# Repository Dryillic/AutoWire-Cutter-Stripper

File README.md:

# AutoWire-Cutter-Stripper

This repository is for documenting the process and project of creating our own automatic wire cutter.
The device will be able to take input from the user regarding wire length, options and number of wires.

The original inspiration for this project came from Reddit user "Maclsk" on the subreddit /r/specializedtools, link here: https://www.reddit.com/r/specializedtools/comments/78wd32/i_made_a_specialized_tool_for_cutting_wire/
Our goal is to create a similar device with autostripping for our workplace.

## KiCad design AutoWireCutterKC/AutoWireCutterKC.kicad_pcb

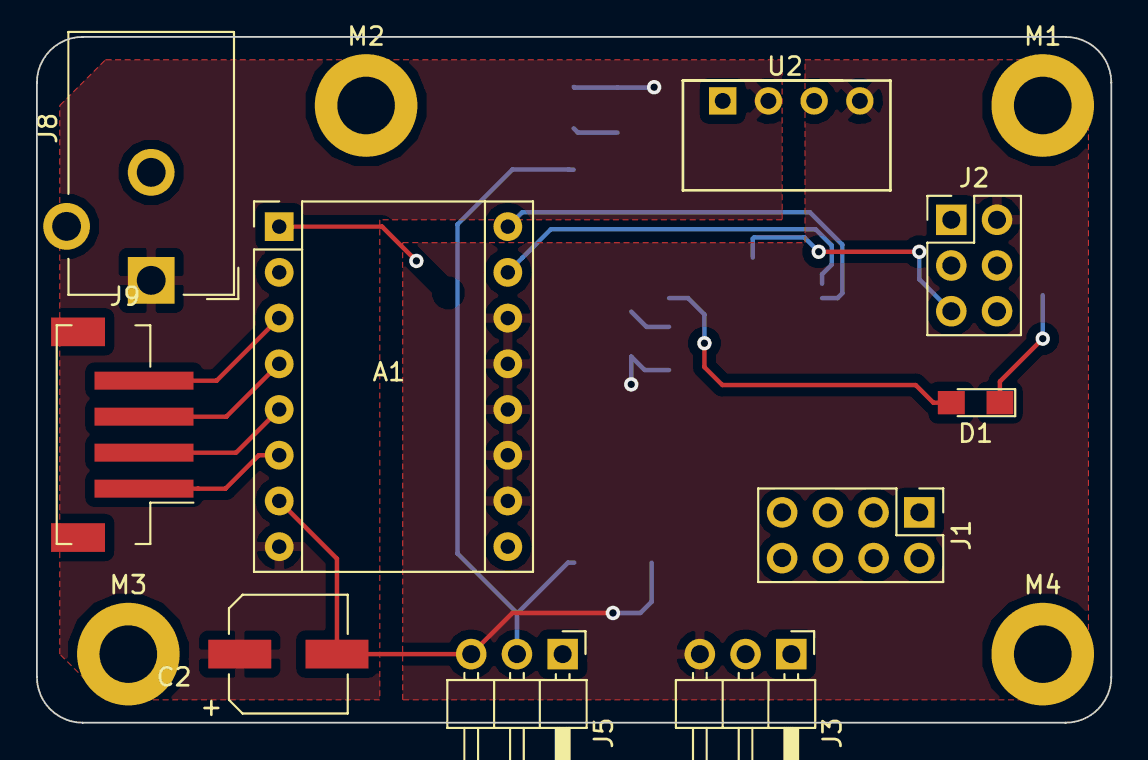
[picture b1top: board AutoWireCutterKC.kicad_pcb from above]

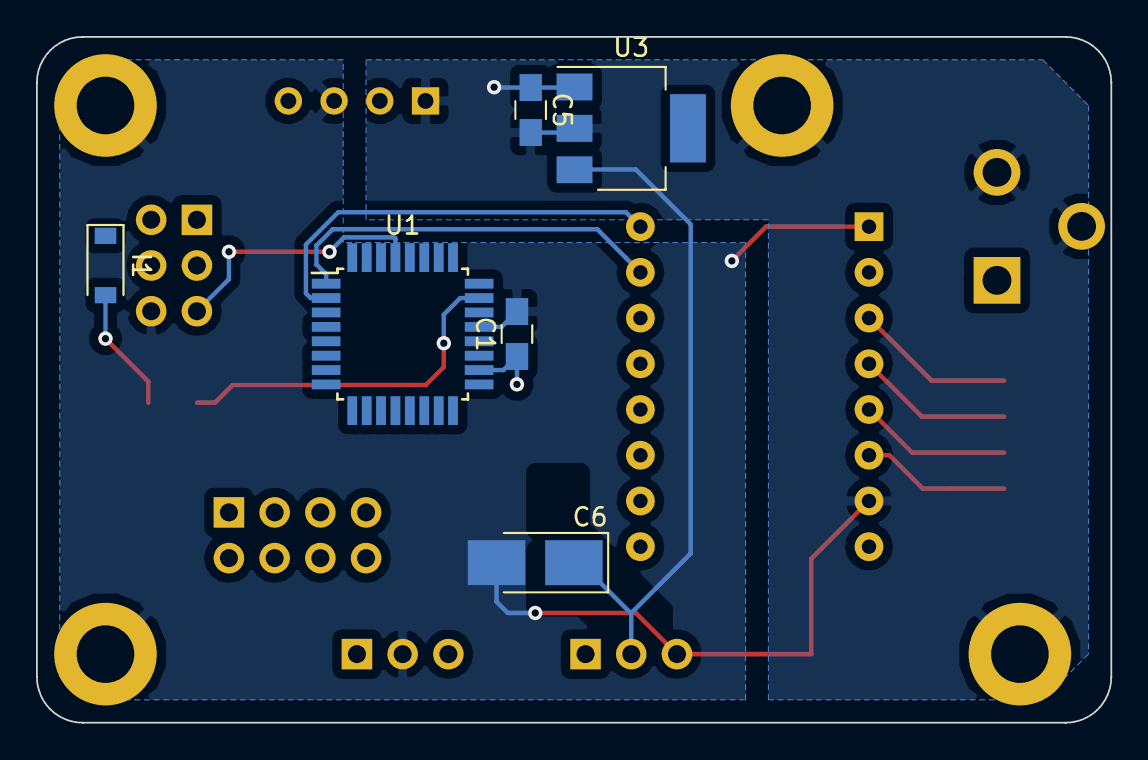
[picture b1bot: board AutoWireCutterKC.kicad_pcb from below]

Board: 2 copper layers, 59.7 x 38.1 mm, 20 parts (6 on the bottom side), 25 nets.

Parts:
A1: Pololu_Breakout_DRV8825; Pololu_Breakout-16_15.2x20.3mm
C1: 100n; C_0805_HandSoldering
C2: 100u; CP_Elec_6.3x7.7
C5: 1u; C_0805_HandSoldering
C6: 3.3u; CP_Tantalum_Case-B_EIA-3528-21_Hand
D1: LED; LED_0805_HandSoldering
I1: NSI50010YT1G; D_SOD-123
J1: LCD I/O; Pin_Header_Straight_2x04_Pitch2.54mm
J2: ISP; Pin_Header_Straight_2x03_Pitch2.54mm
J3: LCD; Pin_Header_Angled_1x03_Pitch2.54mm
J5: Servo; Pin_Header_Angled_1x03_Pitch2.54mm
J8: Barrel_Jack; Barrel_Jack_CUI_PJ-102AH
J9: Stepper; JST_PH_B4B_StressReliefCorrect
M1, M2, M3, M4: Conn_01x01_Male; MountingHole_3.2mm_M3_ISO7380_Pad
U1: ATMEGA328P-AU; TQFP-32_7x7mm_Pitch0.8mm
U2: CRE1S1205SC; CRE1S1205SC_DC_to_DC
U3: LT1129-5.0_SOT223; SOT-223

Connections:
+5V: C6.1, J5.2, U3.3
+5VL: A1.10, A1.11, A1.12, A1.13, A1.14, C1.1, J2.2, J3.3, U1.4, U1.6, U1.18, U2.4
+12V: A1.8, C2.1, C5.1, J8.1, U2.2, U3.1
GND: A1.7, C2.2, C5.2, C6.2, I1.1, J5.3, J8.2, J8.3, M2.1, M3.1, U2.1, U3.2
GNDREF: A1.1, C1.2, J2.6, J3.2, M1.1, M4.1, U1.3, U1.5, U1.21, U2.3
unnamed: A1.3, J9.4
unnamed: A1.4, J9.3
unnamed: A1.5, J9.2
unnamed: A1.6, J9.1
unnamed: A1.9, U1.32
unnamed: A1.15, U1.1
unnamed: A1.16, U1.2
unnamed: D1.1, I1.2
unnamed: D1.2, U1.23
unnamed: J1.1, U1.12
unnamed: J1.2, U1.13
unnamed: J1.3, U1.14
unnamed: J1.4, J2.4, U1.15
unnamed: J1.5, J2.1, U1.16
unnamed: J1.6, J2.3, U1.17
unnamed: J1.7, U1.7
unnamed: J1.8, U1.8
unnamed: J2.5, U1.29
unnamed: J3.1, U1.31
unnamed: J5.1, U1.10

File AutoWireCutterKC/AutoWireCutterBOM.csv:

Source:,C:/Users/dnatov/Documents/GitHub/AutoWire-Cutter-Stripper/AutoWireCutterKC/AutoWireCutterKC.sch,,,,,
Date:,6/14/2018 12:04,,,,,
Tool:,Eeschema 4.0.7,,,,,
Generator:,C:/Program Files (x86)/KiCad/bin/scripting/plugins/bom_csv_grouped_by_value.py,,,,,
Component Count:,20,,,,,
,,,,,,
Individual Components:,,,,,,
,,,,,,
Item,Qty,Reference(s),Value,LibPart,Footprint,Datasheet
,,A1,Pololu_Breakout_DRV8825,Driver_Motor:Pololu_Breakout_DRV8825,Module:Pololu_Breakout-16_15.2x20.3mm,
,,C1,100n,device:C,Capacitors_SMD:C_0805_HandSoldering,
,,C2,100u,device:CP,Capacitors_SMD:CP_Elec_6.3x7.7,
,,C3,1u,device:C,Capacitors_SMD:C_0805_HandSoldering,
,,C4,1u,device:C,Capacitors_SMD:C_0805_HandSoldering,
,,C5,1u,device:C,Capacitors_SMD:C_0805_HandSoldering,
,,C6,3.3u,device:CP1,Capacitors_Tantalum_SMD:CP_Tantalum_Case-B_EIA-3528-21_Hand,
,,J1,LCD I/O,conn:Conn_01x08,Pin_Headers:Pin_Header_Straight_2x04_Pitch2.54mm,
,,J2,ISP,conn:Conn_02x03_Odd_Even,Pin_Headers:Pin_Header_Straight_2x03_Pitch2.54mm,
,,J3,LCD Serial,conn:Conn_01x02,Pin_Headers:Pin_Header_Angled_1x02_Pitch2.54mm,
,,J5,LCD Power,conn:Conn_01x02,Pin_Headers:Pin_Header_Angled_1x02_Pitch2.54mm,
,,J6,Servo,conn:Conn_01x03,Pin_Headers:Pin_Header_Angled_1x03_Pitch2.54mm,
,,J8,Barrel_Jack,conn:Barrel_Jack,Connectors:Barrel_Jack_CUI_PJ-102AH,
,,J9,Stepper,conn:Conn_01x04,S4B-PH-SM4-TB,
,,M1,Conn_01x01_Male,conn:Conn_01x01_Male,,
,,M2,Conn_01x01_Male,conn:Conn_01x01_Male,,
,,M3,Conn_01x01_Male,conn:Conn_01x01_Male,,
,,U1,ATMEGA328P-AU,atmel:ATMEGA328P-AU,Housings_QFP:TQFP-32_7x7mm_Pitch0.8mm,
,,U2,MCP1700_SOT23,regul:MCP1700-5002E_SOT23,TO_SOT_Packages_SMD:SOT-23,
,,U3,LT1129-5.0_SOT223,regul:LT1129-5.0_SOT223,TO_SOT_Packages_SMD:SOT-223,
,,,,,,
,,,,,,
,,,,,,
Collated Components:,,,,,,
,,,,,,
Item,Qty,Reference(s),Value,LibPart,Footprint,Datasheet
1,1,A1,Pololu_Breakout_DRV8825,Driver_Motor:Pololu_Breakout_DRV8825,Module:Pololu_Breakout-16_15.2x20.3mm,
2,1,C1,100n,device:C,Capacitors_SMD:C_0805_HandSoldering,
3,1,C2,100u,device:CP,Capacitors_SMD:CP_Elec_6.3x7.7,
4,3,"C3, C4, C5",1u,device:C,Capacitors_SMD:C_0805_HandSoldering,
5,1,C6,3.3u,device:CP1,Capacitors_Tantalum_SMD:CP_Tantalum_Case-B_EIA-3528-21_Hand,
6,1,J1,LCD I/O,conn:Conn_01x08,Pin_Headers:Pin_Header_Straight_2x04_Pitch2.54mm,
7,1,J2,ISP,conn:Conn_02x03_Odd_Even,Pin_Headers:Pin_Header_Straight_2x03_Pitch2.54mm,
8,1,J3,LCD Serial,conn:Conn_01x02,Pin_Headers:Pin_Header_Angled_1x02_Pitch2.54mm,
9,1,J5,LCD Power,conn:Conn_01x02,Pin_Headers:Pin_Header_Angled_1x02_Pitch2.54mm,
10,1,J6,Servo,conn:Conn_01x03,Pin_Headers:Pin_Header_Angled_1x03_Pitch2.54mm,
11,1,J8,Barrel_Jack,conn:Barrel_Jack,Connectors:Barrel_Jack_CUI_PJ-102AH,
12,1,J9,Stepper,conn:Conn_01x04,Pin_Headers:Pin_Header_Straight_1x04_Pitch2.54mm,
13,3,"M1, M2, M3",Conn_01x01_Male,conn:Conn_01x01_Male,,
14,1,U1,ATMEGA328P-AU,atmel:ATMEGA328P-AU,Housings_QFP:TQFP-32_7x7mm_Pitch0.8mm,
15,1,U2,MCP1700_SOT23,regul:MCP1700-5002E_SOT23,TO_SOT_Packages_SMD:SOT-23,
16,1,U3,LT1129-5.0_SOT223,regul:LT1129-5.0_SOT223,TO_SOT_Packages_SMD:SOT-223,

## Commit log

2018-01-05 Add files via upload
    Serial Tx/Rx enable for the 328P. Also sets up a stream to serial so "printf" can be used to send ascii to a serial target.
2018-01-15 Add files via upload
    4x4 Keypad and LCD to display it. Still needs refining. Keypad input not saved, just a general read of a 4x4 pad.
2018-05-20 Added Stepper Library and Test Code
2018-05-20 Added demo video of Stepper Driver
2018-05-20 Updated library with working Runtostep function
    Additionally added better explanation of Runtostep in example main
2018-05-26 Create Servo Library Folder
2018-05-26 Added Servo Library and Ex Code
2018-05-26 Move to Stepper Library Folder
2018-05-26 Move ex code to StepperLibrary Folder
2018-06-05 Adding KiCad Files
2018-06-06 Update uC Layout
    Power is next, runout sensor planned.
2018-06-11 Schematic Finished
    TODO: Double check connections
2018-06-12 Working on footprints
    in progress
2018-06-12 Finished Footprints
    Refer to sch for generating BOM
2018-06-12 PCB Populated
    Traces needed
2018-06-12 Moving around footprints
    Changing spacing and connectors
2018-06-13 PCB Redesign
    Started on traces
2018-06-13 Rewiring - Layout changed again...
2018-06-13 Update bad file
2018-06-14 Schematic almost done
2018-06-14 Final Version
    Board edge cuts need updating. Otherwise ready to order.
2018-06-14 Edge cuts fixed
2018-06-14 Added board pictures
    design finalized in OshPark. Ready to order
2018-06-14 BOM Generated
2018-06-15 Rev A
    Updated BOM with missing Footprint
2018-07-01 Add files via upload
    Wirecutter Keypad Debounced, Using Timer 2 (CTC Mode) and with a slow repeat of key when button is held.
2018-07-04 Editing Schematic
    new rev needs more changes
2018-07-04 Schematic Rev B
    Changed footprint and silk screen issues
2018-07-04 Schematic Rev B
    Moved silk screen, motor con through holes widened, motor connector fit on top.
2018-07-29 Added Pinout for Keypad, Began schematic work for future boards
2018-07-30 Added Main Code
    In Progress. Timer 1 of Stepper needs work.
2018-08-09 ISP header pinout added
    conventional pinout for AVR used
2018-08-10 In Progress: Changing Schematic
    Rev C
2018-08-20 Board RevC
    Added DC-to-DC converter for isolation, LED for status indication, increased board size and mounting holes and changed pin allocations for more efficient programming.
2018-08-30 Work on PCB layout
2018-09-20 Reworked Libraries
    Fixed bug involving stepper not rotating. Taking things out of ISR helped. Servo wasn't responding because of incorrect DDRD register
2018-09-22 Initial CAD Model for Testing
2018-09-28 CAD Beta
    Functional prototype CAD. Not Final
2018-09-30 Significant Base Plate Changes
    Hopefully working prototype. Base will be added in the following days.
2018-10-01 Base Plate Finished. Base needs DC Barrel added
2018-10-02 Final CAD
2018-10-02 Final CAD - Base Missing
2018-10-02 Final CAD - Updated STLs
2018-10-02 Fixed CAD error
2018-10-04 Added Custom Idler
